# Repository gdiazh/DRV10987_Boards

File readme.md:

# DRV10987 Boards
Different custom appication eagle-boards for drv10987 BLDC motor driver

## Brief

* DRV10987: PC104-board application using a single driver and atmega328 uC
* DRV10987_SAMD21uC: PC104-board application using three drivers and samd21 uC
* mini_v1: small square board using a single driver and atmega328 uC
* mini_v2: small circle board for a single driver
* mini_v2: small circle board for a single driver
* uC_mini_v2: atmega328 uC mini-circular board
* uCsamd21_mini: samd21 uC mini-circular board

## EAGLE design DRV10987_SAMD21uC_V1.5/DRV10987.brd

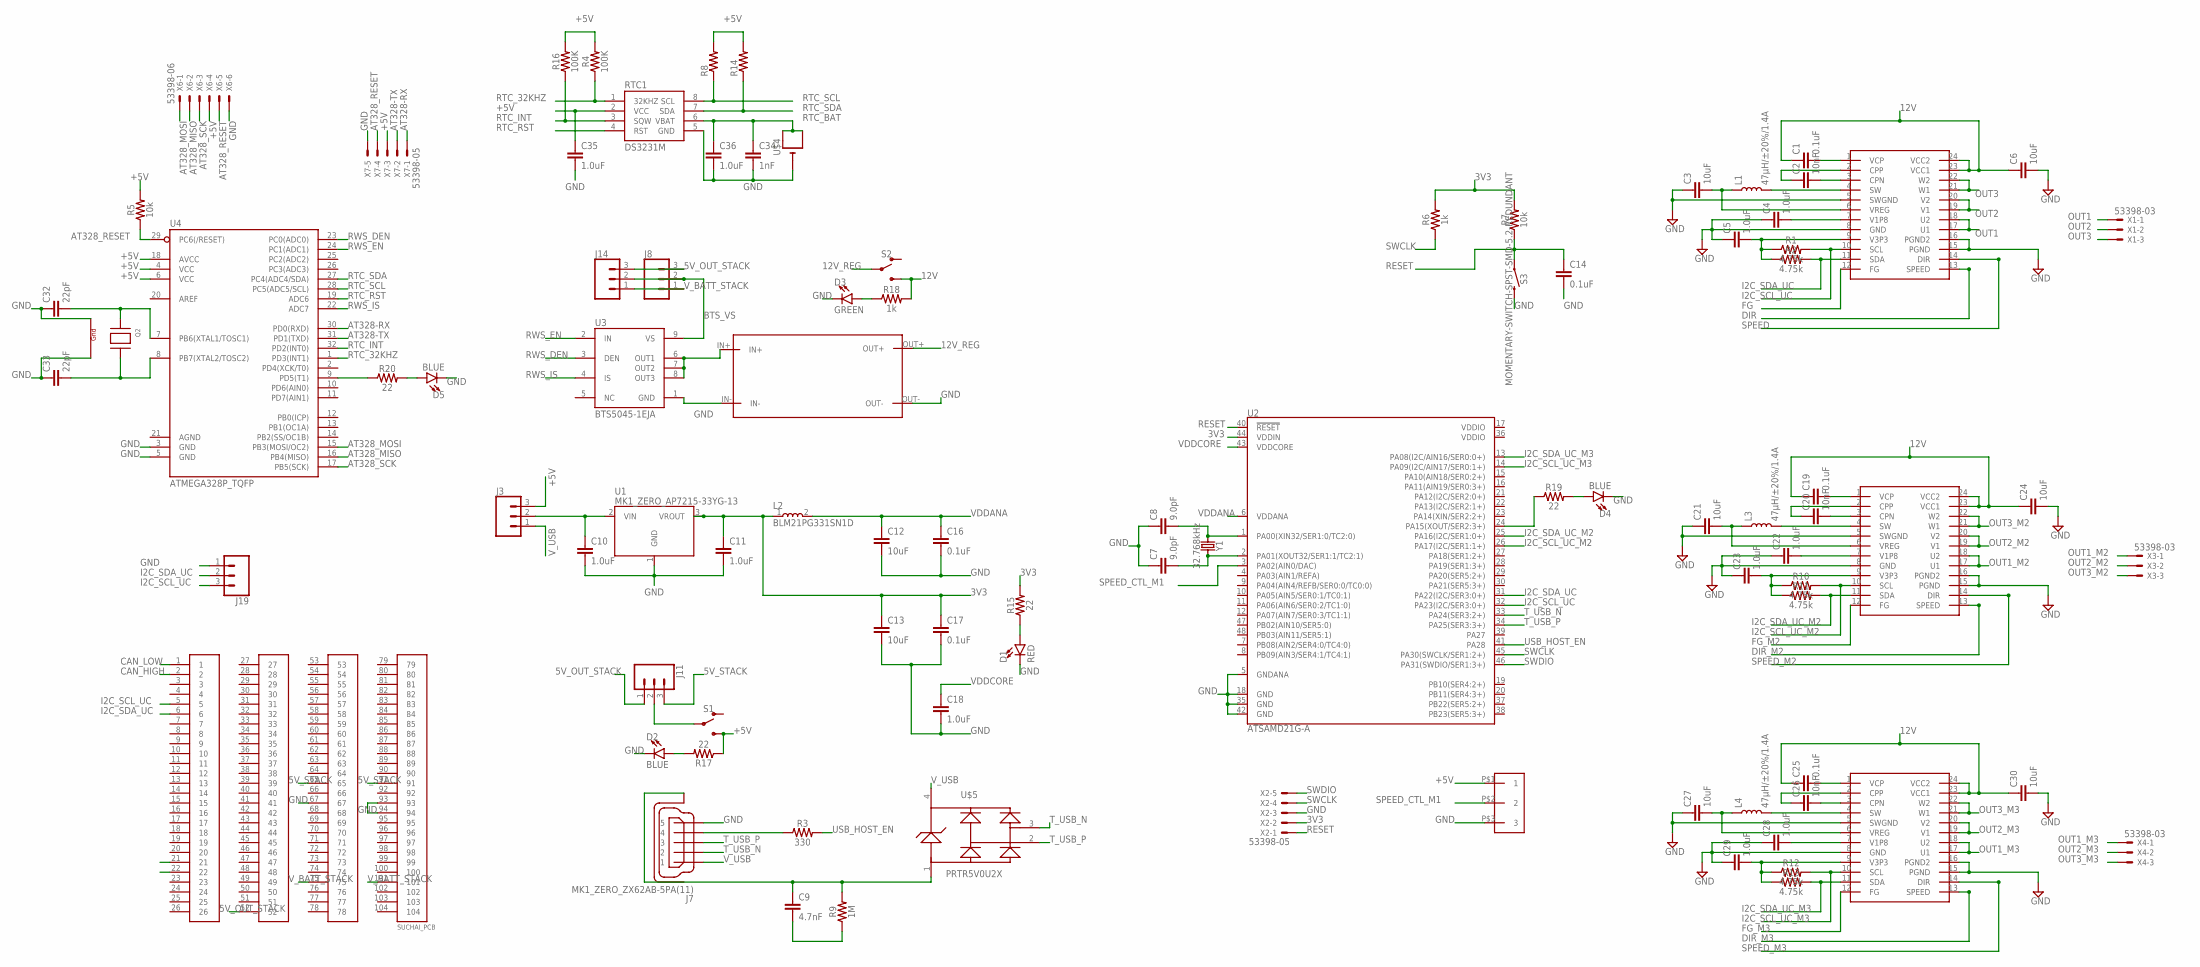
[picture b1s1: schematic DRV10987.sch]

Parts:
C1, C14, C16, C17, C19, C25: 0.1uF; 0805
C2, C20, C26: 10nF; 0805
C3, C6, C12, C13, C21, C24, C27, C30: 10uF; 0805
C4, C5, C10, C11, C18, C22, C23, C28, C29: 1.0uF; 0805
C7, C8: 9.0pF; 0603
C9: 4.7nF; 0603
C32, C33: 22pF; 0603
C34: 1nF; 0603
C35, C36: 1.0uF; 0402
D1: RED; LED-0603
D2, D4, D5: BLUE; LED-0603
D3: GREEN; LED-0603
J1: SUCHAI_PCB
J3: CONN_03LOCK_LONGPADS; 1X03_LOCK_LONGPADS
J7: MK1_ZERO_ZX62AB-5PA(11); MK1_ZERO_USBMICRO-ZX62-AB-5PA
J8, J11, J14, J19: CONN_03LOCK; 1X03_LOCK
L1, L3, L4: 47µH/±20%/1.4A; SRN6045
L2: BLM21PG331SN1D; INDC2012X87
Q2: XTAL-4-3225; NX3225
R1, R2, R10, R11, R12, R13: 4.75k; 0805
R3: 330; 0603
R4, R16: 100K; 0402
R5, R7: 10k; 0603
R6, R18: 1k; 0603
R8, R14: R-US_R0402; R0402
R9: 1M; 0603
R15, R17, R19, R20: 22; 0603
RTC1: DS3231M; SO08
S1, S2: SWITCH-SPDT-PTH-11.6X4.0MM; SWITCH_SPDT_PTH_11.6X4.0MM
S3: MOMENTARY-SWITCH-SPST-SMD-5.2-REDUNDANT; TACTILE_SWITCH_SMD_5.2MM
U1: MK1_ZERO_AP7215-33YG-13; MK1_ZERO_SOT150P400X160-3N
U2: ATSAMD21G-A; TQFP-48
U3: BTS5045-1EJA; SOIC127P600X170-9N
U4: ATMEGA328P_TQFP; TQFP32-08
U$1, U$6, U$7: DRV10987
U$2: XL6009E1_MODULE
U$3: CONN_03_SMD_SMALL
U$4: CR1220SMT; CR1220-SMD
U$5: ARDUINO_PRTR5V0U2XB; ARDUINO_SOT143B
X1, X3, X4: 53398-03
X2, X7: 53398-05
X6: 53398-06
Y1: 32.768kHz; CRYSTAL-SMD-3.2X1.5MM

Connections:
3V3: C11.1, C13.1, C17.1, L2.1, R6.2, R7.2, R15.2, U1.3 (VROUT), U2.44 (VDDIN), X2.2
5V_OUT_STACK: J1.52, J8.3, J11.1, J14.3
5V_STACK: J1.65, J1.91, J11.3
12V: C1.1, C6.1, C19.1, C24.1, C25.1, C30.1, R18.2, S2.3 (S), U$1.23 (VCC1), U$1.24 (VCC2), U$6.23 (VCC1), U$6.24 (VCC2), U$7.23 (VCC1), U$7.24 (VCC2)
12V_REG: S2.2, U$2.OUT+
+5V: C35.1, J3.3, R4.2, R5.2, R8.2, R14.2, R16.2, R17.1, RTC1.2 (VCC), S1.3 (S), U4.4 (VCC), U4.6 (VCC), U4.18 (AVCC), U$3.P$1 (1), X6.4, X7.3
AT328-RX: U4.30 (PD0(RXD)), X7.1
AT328-TX: U4.31 (PD1(TXD)), X7.2
AT328_MISO: U4.16 (PB4(MISO)), X6.2
AT328_MOSI: U4.15 (PB3(MOSI/OC2)), X6.1
AT328_RESET: R5.1, U4.29 (PC6(/RESET)), X6.5, X7.4
AT328_SCK: U4.17 (PB5(SCK)), X6.3
BTS_VS: J8.2, J14.2, U3.9 (VS)
CAN_HIGH: J1.2
CAN_LOW: J1.1
DIR: U$1.13 (SPEED)
DIR_M2: U$6.13 (SPEED)
DIR_M3: U$7.13 (SPEED)
FG: U$1.12 (FG)
FG_M2: U$6.12 (FG)
FG_M3: U$7.12 (FG)
GND: C3.1, C4.1, C5.1, C6.2, C7.1, C8.1, C10.2, C11.2, C12.2, C13.2, C14.2, C16.2, C17.2, C18.2, C21.1, C22.1, C23.1, C24.2, C27.1, C28.1, C29.1, C30.2, C32.1, C33.1, C34.2, C35.2, C36.2, D1.C, D2.C, D3.C, D4.C, D5.C, J1.67, J1.93, J1.94, J7.5, J19.1, Q2.2 (G2), Q2.4 (G1), RTC1.5 (GND), S3.3 (2), S3.4 (2), U1.1 (GND), U2.5 (GNDANA), U2.18 (GND), U2.35 (GND), U2.42 (GND), U3.1 (GND), U4.3 (GND), U4.5 (GND), U$1.5 (SWGND), U$1.8 (GND), U$1.15 (PGND), U$1.16 (PGND2), U$2.IN-, U$2.OUT-, U$3.P$3 (3), U$4.-, U$6.5 (SWGND), U$6.8 (GND), U$6.15 (PGND), U$6.16 (PGND2), U$7.5 (SWGND), U$7.8 (GND), U$7.15 (PGND), U$7.16 (PGND2), X2.3, X6.6, X7.5
I2C_SCL_UC: J1.5, J19.3, R1.2, U2.32 (PA23(I2C/SER3:0+)), U$1.10 (SCL)
I2C_SCL_UC_M2: R10.2, U2.26 (PA17(I2C/SER1:1+)), U$6.10 (SCL)
I2C_SCL_UC_M3: R12.2, U2.14 (PA09(I2C/AIN17/SER0:1+)), U$7.10 (SCL)
I2C_SDA_UC: J1.6, J19.2, R2.2, U2.31 (PA22(I2C/SER3:0+)), U$1.11 (SDA)
I2C_SDA_UC_M2: R11.2, U2.25 (PA16(I2C/SER1:0+)), U$6.11 (SDA)
I2C_SDA_UC_M3: R13.2, U2.13 (PA08(I2C/AIN16/SER0:0+)), U$7.11 (SDA)
unnamed: C1.2, U$1.1 (VCP)
unnamed: C2.1, U$1.2 (CPP)
unnamed: C2.2, U$1.3 (CPN)
unnamed: L1.2, U$1.4 (SW)
unnamed: J11.2, S1.2
unnamed: C3.2, L1.1, U$1.6 (VREG)
unnamed: C4.2, U$1.7 (V1P8)
unnamed: C7.2, U2.2 (PA01(XOUT32/SER1:1/TC2:1)), Y1.P$2 (2)
unnamed: C5.2, R1.1, R2.1, U$1.9 (V3P3)
unnamed: C8.2, U2.1 (PA00(XIN32/SER1:0/TC2:0)), Y1.P$1 (1)
unnamed: J7.4, R3.1
unnamed: U3.6 (OUT1), U3.7 (OUT2), U3.8 (OUT3), U$2.IN+
unnamed: C32.2, Q2.1 (X1), U4.7 (PB6(XTAL1/TOSC1))
unnamed: C33.2, Q2.3 (X2), U4.8 (PB7(XTAL2/TOSC2))
unnamed: D1.A, R15.1
unnamed: C9.1, J7.6 (SH), J7.7 (SH), J7.8 (SH), J7.9 (SH), J7.10 (SH), J7.11 (SH), R9.2, U$5.1
unnamed: C9.2, R9.1
unnamed: C10.1, J3.2, U1.2 (VIN)
unnamed: D2.A, R17.2
unnamed: C19.2, U$6.1 (VCP)
unnamed: C20.1, U$6.2 (CPP)
unnamed: C20.2, U$6.3 (CPN)
unnamed: L3.2, U$6.4 (SW)
unnamed: C21.2, L3.1, U$6.6 (VREG)
unnamed: C22.2, U$6.7 (V1P8)
unnamed: C23.2, R10.1, R11.1, U$6.9 (V3P3)
unnamed: C25.2, U$7.1 (VCP)
unnamed: C26.1, U$7.2 (CPP)
unnamed: C26.2, U$7.3 (CPN)
unnamed: L4.2, U$7.4 (SW)
unnamed: C27.2, L4.1, U$7.6 (VREG)
unnamed: C28.2, U$7.7 (V1P8)
unnamed: C29.2, R12.1, R13.1, U$7.9 (V3P3)
unnamed: D3.A, R18.1
unnamed: D4.A, R19.2
unnamed: R19.1, U2.24 (PA15(XOUT/SER2:3+))
unnamed: D5.A, R20.2
unnamed: R20.1, U4.9 (PD5(T1))
OUT1: U$1.17 (U1), U$1.18 (U2), X1.1
OUT1_M2: U$6.17 (U1), U$6.18 (U2), X3.1
OUT1_M3: U$7.17 (U1), U$7.18 (U2), X4.1
OUT2: U$1.19 (V1), U$1.20 (V2), X1.2
OUT2_M2: U$6.19 (V1), U$6.20 (V2), X3.2
OUT2_M3: U$7.19 (V1), U$7.20 (V2), X4.2
OUT3: U$1.21 (W1), U$1.22 (W2), X1.3
OUT3_M2: U$6.21 (W1), U$6.22 (W2), X3.3
OUT3_M3: U$7.21 (W1), U$7.22 (W2), X4.3
RESET: C14.1, R7.1, S3.1, S3.2 (1), U2.40 (!RESET!), X2.1
RTC_32KHZ: R4.1, RTC1.1 (32KHZ), U4.1 (PD3(INT1))
RTC_BAT: C34.1, C36.1, RTC1.6 (VBAT), U$4.+$1 (+), U$4.+$2 (+1)
RTC_INT: R16.1, RTC1.3 (SQW), U4.32 (PD2(INT0))
RTC_RST: RTC1.4 (RST), U4.19 (ADC6)
RTC_SCL: R8.1, RTC1.8 (SCL), U4.28 (PC5(ADC5/SCL))
RTC_SDA: R14.1, RTC1.7 (SDA), U4.27 (PC4(ADC4/SDA))
RWS_DEN: U3.3 (DEN), U4.23 (PC0(ADC0))
RWS_EN: U3.2 (IN), U4.24 (PC1(ADC1))
RWS_IS: U3.4 (IS), U4.22 (ADC7)
SPEED: U$1.14 (DIR)
SPEED_CTL_M1: U2.3 (PA02(AIN0/DAC)), U$3.P$2 (2)
SPEED_M2: U$6.14 (DIR)
SPEED_M3: U$7.14 (DIR)
SWCLK: R6.1, U2.45 (PA30(SWCLK/SER1:2+)), X2.4
SWDIO: U2.46 (PA31(SWDIO/SER1:3+)), X2.5
T_USB_N: J7.2, U2.33 (PA24(SER3:2+)), U$5.3
T_USB_P: J7.3, U2.34 (PA25(SER3:3+)), U$5.2
USB_HOST_EN: R3.2, U2.41 (PA28)
VDDANA: C12.1, C16.1, L2.2, U2.6 (VDDANA)
VDDCORE: C18.1, U2.43 (VDDCORE)
V_BATT_STACK: J1.75, J1.101, J8.1, J14.1
V_USB: J3.1, J7.1, U$5.4

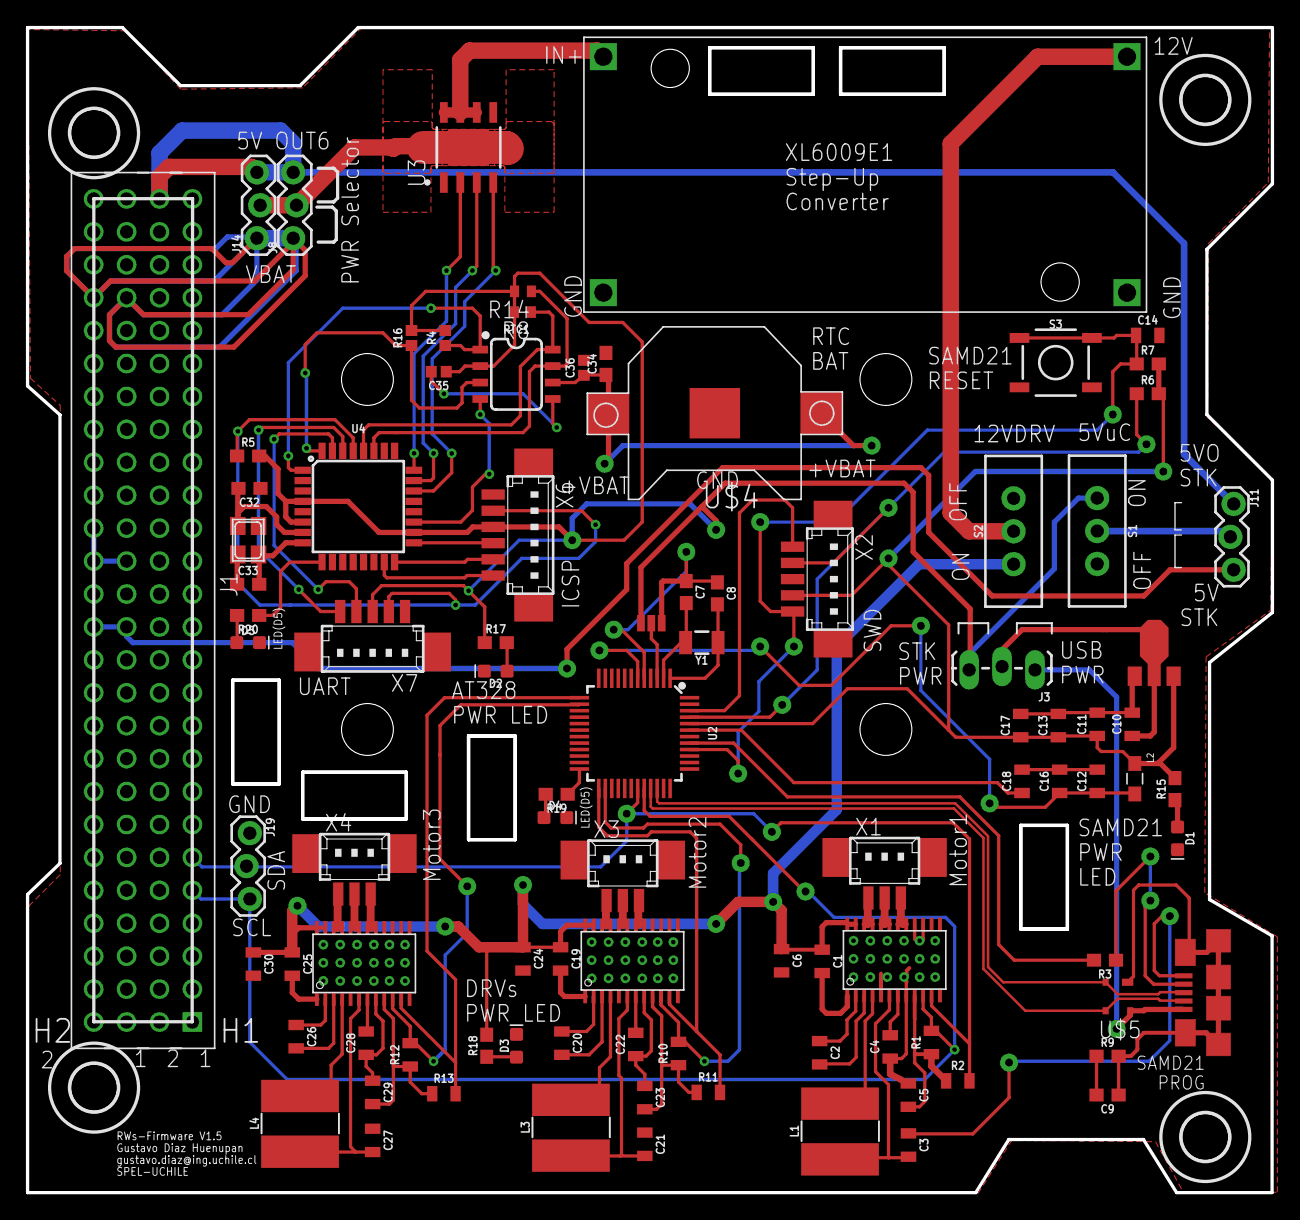
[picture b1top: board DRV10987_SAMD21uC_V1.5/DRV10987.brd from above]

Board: 2 copper layers, 96.0 x 89.9 mm, 93 parts (0 on the bottom side), 87 nets.

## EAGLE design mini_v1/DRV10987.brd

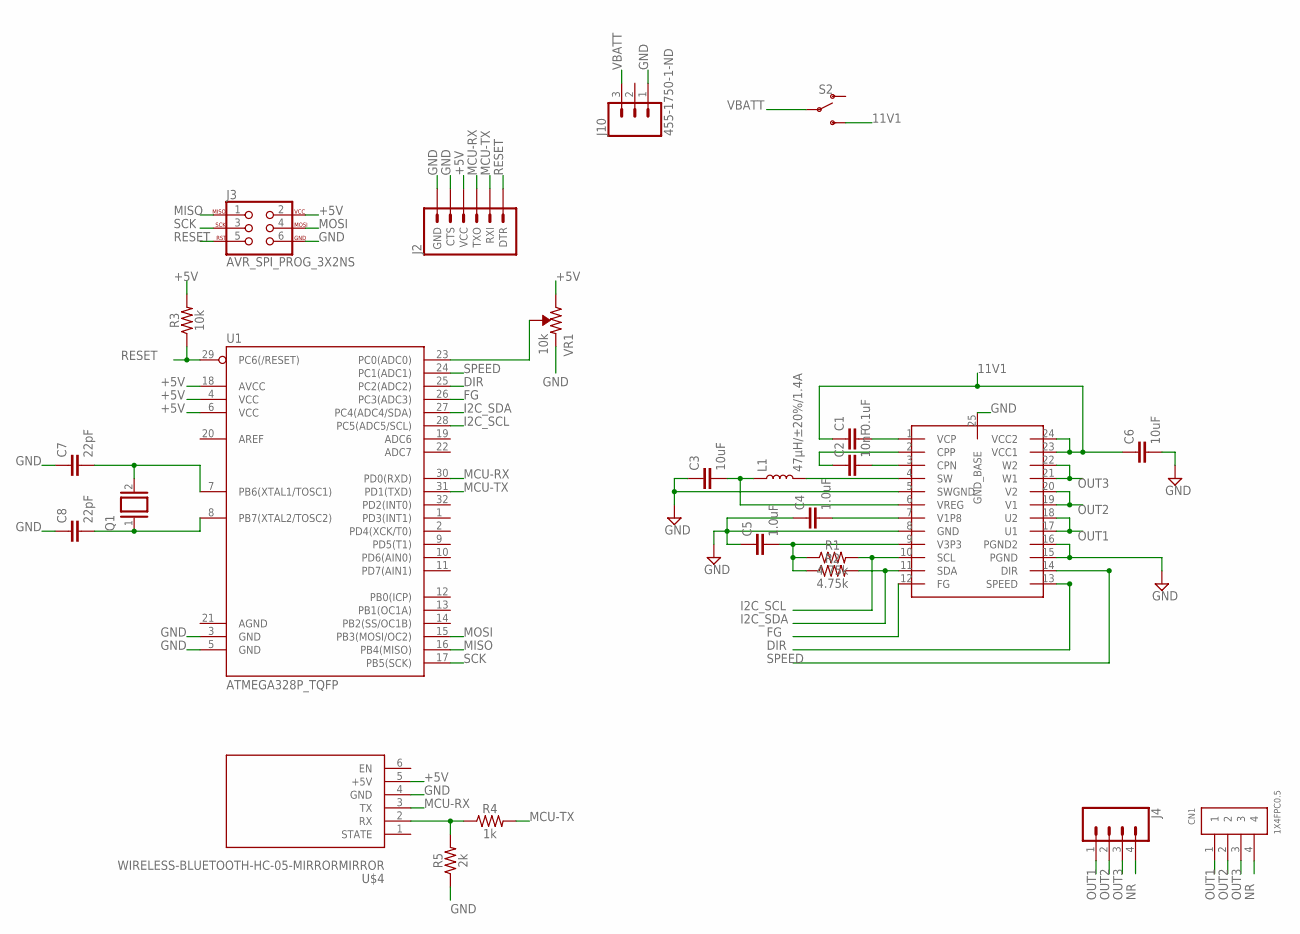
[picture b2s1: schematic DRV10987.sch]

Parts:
C1: 0.1uF; 0805
C2: 10nF; 0805
C3, C6: 10uF; 0805
C4, C5: 1.0uF; 0805
C7, C8: 22pF; 1206
CN1: 1X4FPC0.5; FPC_0.5MM-4
J2: 6_PIN_SERIAL_TARGET; 1X06
J3: AVR_SPI_PROG_3X2NS; 2X3-NS
J4: CONN_04; 1X04
J10: 455-1750-1-ND; 1X03
L1: 47µH/±20%/1.4A; SRN6045
Q1: XTAL/S; QS
R1, R2: 4.75k; 0805
R3: 10k; 1206
R4: 1k; AXIAL-0.3
R5: 2k; AXIAL-0.3
S2: SWITCH-SPDT-PTH-11.6X4.0MM; SWITCH_SPDT_PTH_11.6X4.0MM
U1: ATMEGA328P_TQFP; TQFP32-08
U$1: DRV10987
U$4: WIRELESS-BLUETOOTH-HC-05-MIRRORMIRROR; WIRELESS-BLUETOOTH-HC-05-MIRROR
VR1: 10k; TRIMPOT-PTH-3386U

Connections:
11V1: C1.1, C6.1, S2.3 (S), U$1.23 (VCC1), U$1.24 (VCC2)
+5V: J2.4 (VCC), J3.2, R3.2, U1.4 (VCC), U1.6 (VCC), U1.18 (AVCC), U$4.5 (+5V), VR1.3 (CW)
DIR: U1.25 (PC2(ADC2)), U$1.13 (SPEED)
FG: U1.26 (PC3(ADC3)), U$1.12 (FG)
GND: C3.1, C4.1, C5.1, C6.2, C7.1, C8.1, J2.5 (CTS), J2.6 (GND), J3.6, J10.1, R5.P$1 (1), U1.3 (GND), U1.5 (GND), U$1.5 (SWGND), U$1.8 (GND), U$1.15 (PGND), U$1.16 (PGND2), U$1.25 (GND_BASE), U$4.4 (GND), VR1.1 (CCW)
I2C_SCL: R1.2, U1.28 (PC5(ADC5/SCL)), U$1.10 (SCL)
I2C_SDA: R2.2, U1.27 (PC4(ADC4/SDA)), U$1.11 (SDA)
MCU-RX: J2.3 (TXO), U1.30 (PD0(RXD)), U$4.3 (TX)
MCU-TX: J2.2 (RXI), R4.P$2 (2), U1.31 (PD1(TXD))
MISO: J3.1, U1.16 (PB4(MISO))
MOSI: J3.4, U1.15 (PB3(MOSI/OC2))
unnamed: C1.2, U$1.1 (VCP)
unnamed: C2.1, U$1.2 (CPP)
unnamed: C2.2, U$1.3 (CPN)
unnamed: L1.2, U$1.4 (SW)
unnamed: C3.2, L1.1, U$1.6 (VREG)
unnamed: C4.2, U$1.7 (V1P8)
unnamed: C7.2, Q1.2, U1.7 (PB6(XTAL1/TOSC1))
unnamed: C5.2, R1.1, R2.1, U$1.9 (V3P3)
unnamed: C8.2, Q1.1, U1.8 (PB7(XTAL2/TOSC2))
unnamed: R4.P$1 (1), R5.P$2 (2), U$4.2 (RX)
unnamed: U1.23 (PC0(ADC0)), VR1.2 (WIPER)
NR: CN1.4, J4.4
OUT1: CN1.1, J4.1, U$1.17 (U1), U$1.18 (U2)
OUT2: CN1.2, J4.2, U$1.19 (V1), U$1.20 (V2)
OUT3: CN1.3, J4.3, U$1.21 (W1), U$1.22 (W2)
RESET: J2.1 (DTR), J3.5, R3.1, U1.29 (PC6(/RESET))
SCK: J3.3, U1.17 (PB5(SCK))
SPEED: U1.24 (PC1(ADC1)), U$1.14 (DIR)
VBATT: J10.3, S2.2

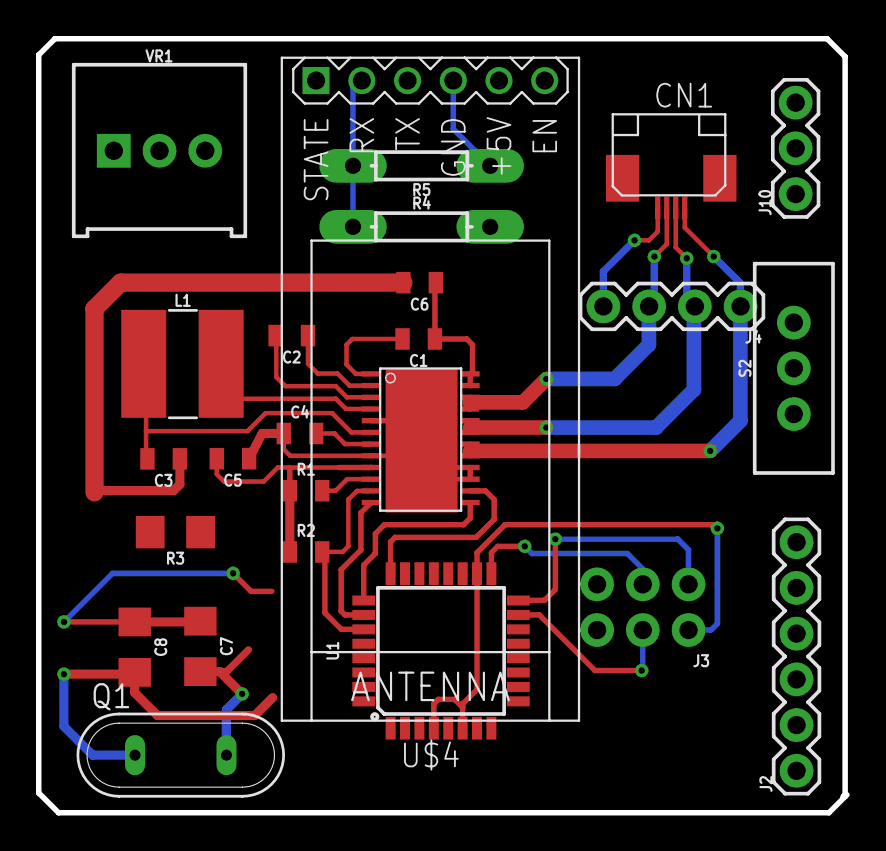
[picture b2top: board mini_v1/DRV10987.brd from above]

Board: 2 copper layers, 44.9 x 43.0 mm, 25 parts (0 on the bottom side), 30 nets.

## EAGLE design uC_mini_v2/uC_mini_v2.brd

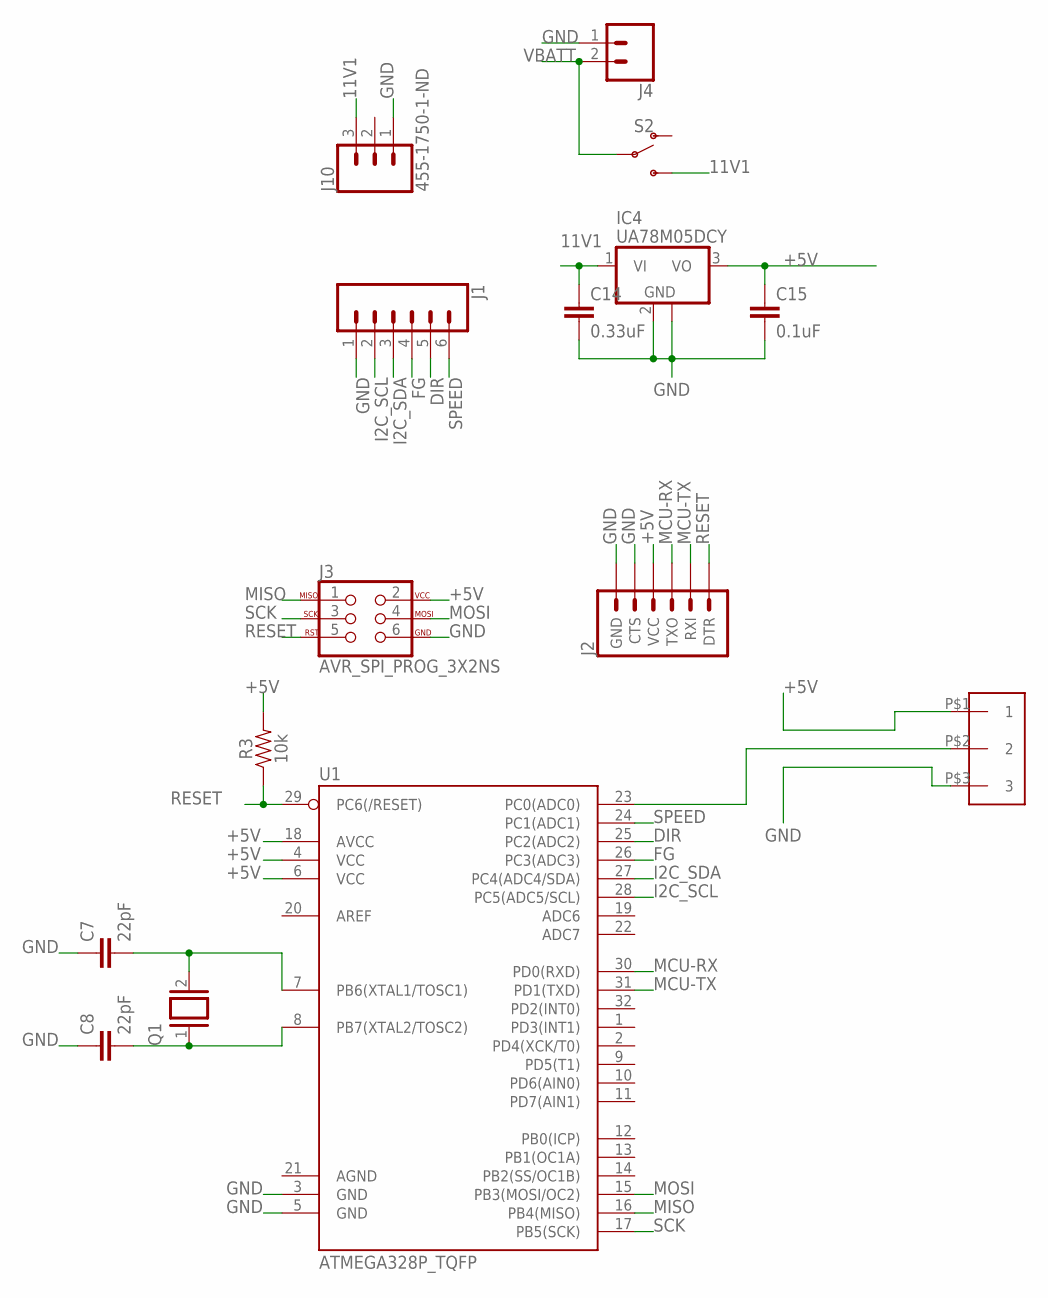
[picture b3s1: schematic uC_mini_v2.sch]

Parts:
C7, C8: 22pF; 1206
C14: 0.33uF; 1206
C15: 0.1uF; 1206
IC4: UA78M05DCY; SOT223
J1: CONN_06LOCK; 1X06_LOCK
J2: 6_PIN_SERIAL_TARGET; 1X06
J3: AVR_SPI_PROG_3X2NS; 2X3-NS
J4: CONN_02LOCK; 1X02_LOCK
J10: 455-1750-1-ND; 1X03
Q1: XTAL/S; QS
R3: 10k; 1206
S2: SWITCH-SPDT-PTH-11.6X4.0MM; SWITCH_SPDT_PTH_11.6X4.0MM
U1: ATMEGA328P_TQFP; TQFP32-08
U$3: CONN_03_SMD_SMALL

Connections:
11V1: C14.1, IC4.1 (VI), J10.3, S2.3 (S)
+5V: C15.1, IC4.3 (VO), J2.4 (VCC), J3.2, R3.2, U1.4 (VCC), U1.6 (VCC), U1.18 (AVCC), U$3.P$1 (1)
DIR: J1.5, U1.25 (PC2(ADC2))
FG: J1.4, U1.26 (PC3(ADC3))
GND: C7.1, C8.1, C14.2, C15.2, IC4.2 (GND), IC4.4 (GND), J1.1, J2.5 (CTS), J2.6 (GND), J3.6, J4.1, J10.1, U1.3 (GND), U1.5 (GND), U$3.P$3 (3)
I2C_SCL: J1.2, U1.28 (PC5(ADC5/SCL))
I2C_SDA: J1.3, U1.27 (PC4(ADC4/SDA))
MCU-RX: J2.3 (TXO), U1.30 (PD0(RXD))
MCU-TX: J2.2 (RXI), U1.31 (PD1(TXD))
MISO: J3.1, U1.16 (PB4(MISO))
MOSI: J3.4, U1.15 (PB3(MOSI/OC2))
unnamed: C7.2, Q1.2, U1.7 (PB6(XTAL1/TOSC1))
unnamed: C8.2, Q1.1, U1.8 (PB7(XTAL2/TOSC2))
unnamed: U1.23 (PC0(ADC0)), U$3.P$2 (2)
RESET: J2.1 (DTR), J3.5, R3.1, U1.29 (PC6(/RESET))
SCK: J3.3, U1.17 (PB5(SCK))
SPEED: J1.6, U1.24 (PC1(ADC1))
VBATT: J4.2, S2.2

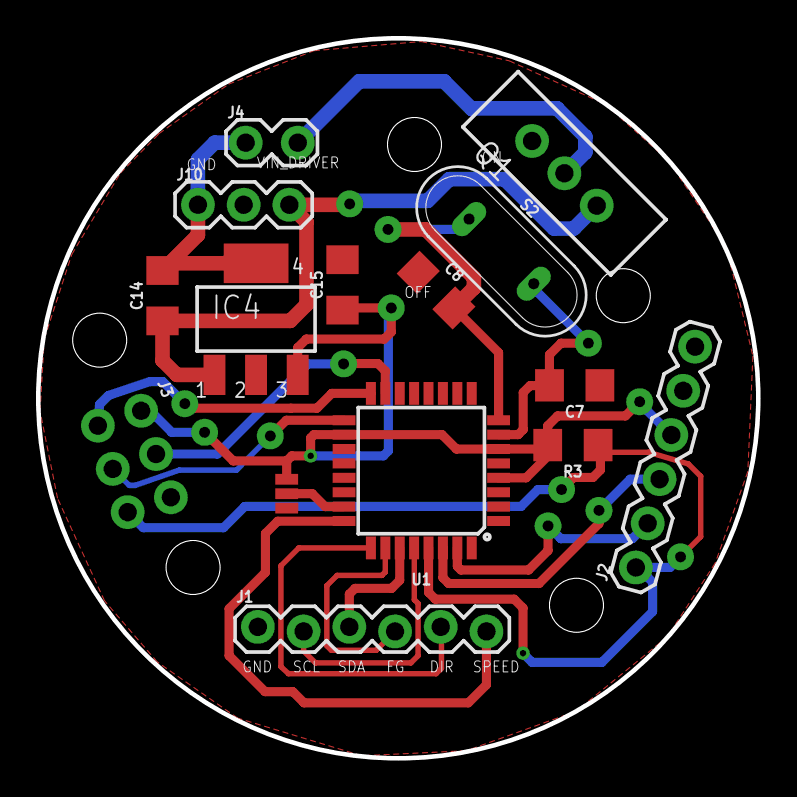
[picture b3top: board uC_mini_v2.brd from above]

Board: 2 copper layers, 40.0 x 40.0 mm, 15 parts (0 on the bottom side), 18 nets.

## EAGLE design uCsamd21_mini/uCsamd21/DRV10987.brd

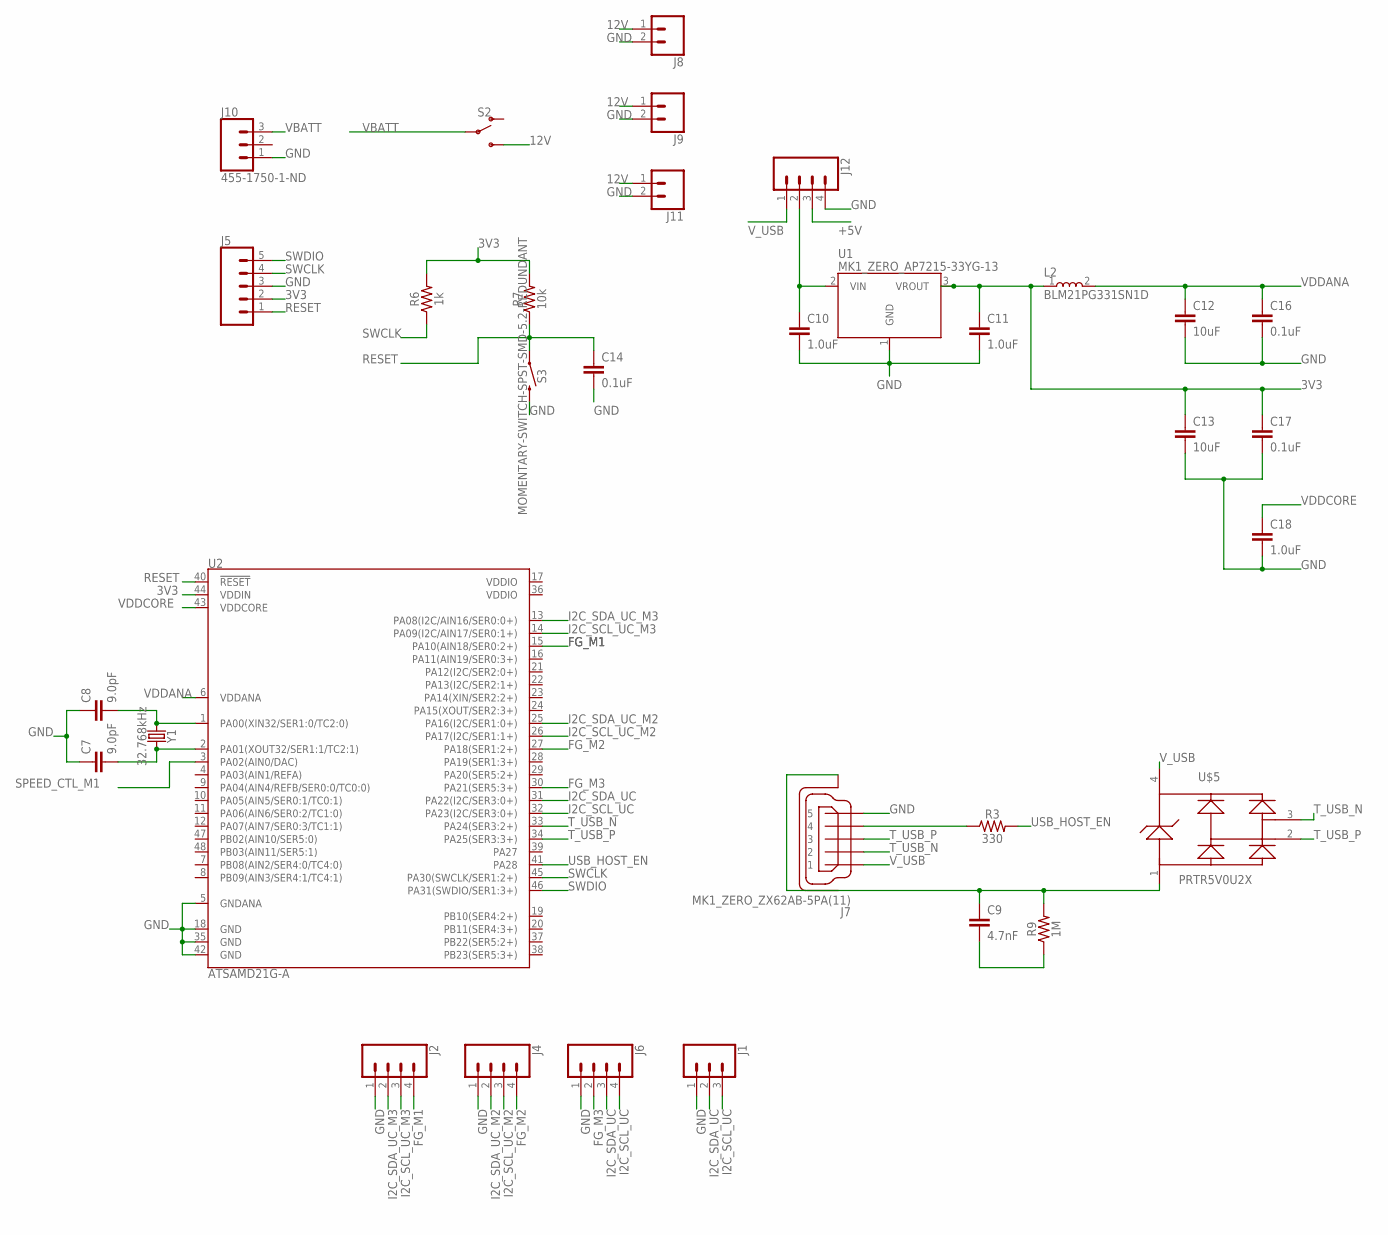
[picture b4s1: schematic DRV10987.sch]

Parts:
C7, C8: 9.0pF; 0603
C9: 4.7nF; 0603
C10, C11, C18: 1.0uF; 0805
C12, C13: 10uF; 0805
C14, C16, C17: 0.1uF; 0805
J1: CONN_03LOCK; 1X03_LOCK
J2, J4, J6, J12: CONN_04LOCK; 1X04_LOCK
J5: CONN_05LOCK_LONGPADS; 1X05_LOCK_LONGPADS
J7: MK1_ZERO_ZX62AB-5PA(11); MK1_ZERO_USBMICRO-ZX62-AB-5PA
J8, J9, J11: CONN_02LOCK; 1X02_LOCK
J10: 455-1750-1-ND; 1X03
L2: BLM21PG331SN1D; INDC2012X87
R3: 330; 0603
R6: 1k; 0603
R7: 10k; 0603
R9: 1M; 0603
S2: SWITCH-SPDT-PTH-11.6X4.0MM; SWITCH_SPDT_PTH_11.6X4.0MM
S3: MOMENTARY-SWITCH-SPST-SMD-5.2-REDUNDANT; TACTILE_SWITCH_SMD_5.2MM
U1: MK1_ZERO_AP7215-33YG-13; MK1_ZERO_SOT150P400X160-3N
U2: ATSAMD21G-A; TQFP-48
U$5: ARDUINO_PRTR5V0U2XB; ARDUINO_SOT143B
Y1: 32.768kHz; CRYSTAL-SMD-3.2X1.5MM

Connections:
3V3: C11.1, C13.1, C17.1, J5.2, L2.1, R6.2, R7.2, U1.3 (VROUT), U2.44 (VDDIN)
12V: J8.1, J9.1, J11.1, S2.3 (S)
+5V: J12.3
FG_M1: J2.4, U2.15 (PA10(AIN18/SER0:2+))
FG_M2: J4.4, U2.27 (PA18(SER1:2+))
FG_M3: J6.2, U2.30 (PA21(SER5:3+))
GND: C7.1, C8.1, C10.2, C11.2, C12.2, C13.2, C14.2, C16.2, C17.2, C18.2, J1.1, J2.1, J4.1, J5.3, J6.1, J7.5, J8.2, J9.2, J10.1, J11.2, J12.4, S3.3 (2), S3.4 (2), U1.1 (GND), U2.5 (GNDANA), U2.18 (GND), U2.35 (GND), U2.42 (GND)
I2C_SCL_UC: J1.3, J6.4, U2.32 (PA23(I2C/SER3:0+))
I2C_SCL_UC_M2: J4.3, U2.26 (PA17(I2C/SER1:1+))
I2C_SCL_UC_M3: J2.3, U2.14 (PA09(I2C/AIN17/SER0:1+))
I2C_SDA_UC: J1.2, J6.3, U2.31 (PA22(I2C/SER3:0+))
I2C_SDA_UC_M2: J4.2, U2.25 (PA16(I2C/SER1:0+))
I2C_SDA_UC_M3: J2.2, U2.13 (PA08(I2C/AIN16/SER0:0+))
unnamed: J7.4, R3.1
unnamed: C7.2, U2.2 (PA01(XOUT32/SER1:1/TC2:1)), Y1.P$2 (2)
unnamed: C8.2, U2.1 (PA00(XIN32/SER1:0/TC2:0)), Y1.P$1 (1)
unnamed: C9.1, J7.6 (SH), J7.7 (SH), J7.8 (SH), J7.9 (SH), J7.10 (SH), J7.11 (SH), R9.2, U$5.1
unnamed: C9.2, R9.1
unnamed: C10.1, J12.2, U1.2 (VIN)
RESET: C14.1, J5.1, R7.1, S3.1, S3.2 (1), U2.40 (!RESET!)
SPEED_CTL_M1: U2.3 (PA02(AIN0/DAC))
SWCLK: J5.4, R6.1, U2.45 (PA30(SWCLK/SER1:2+))
SWDIO: J5.5, U2.46 (PA31(SWDIO/SER1:3+))
T_USB_N: J7.2, U2.33 (PA24(SER3:2+)), U$5.3
T_USB_P: J7.3, U2.34 (PA25(SER3:3+)), U$5.2
USB_HOST_EN: R3.2, U2.41 (PA28)
VBATT: J10.3, S2.2
VDDANA: C12.1, C16.1, L2.2, U2.6 (VDDANA)
VDDCORE: C18.1, U2.43 (VDDCORE)
V_USB: J7.1, J12.1, U$5.4

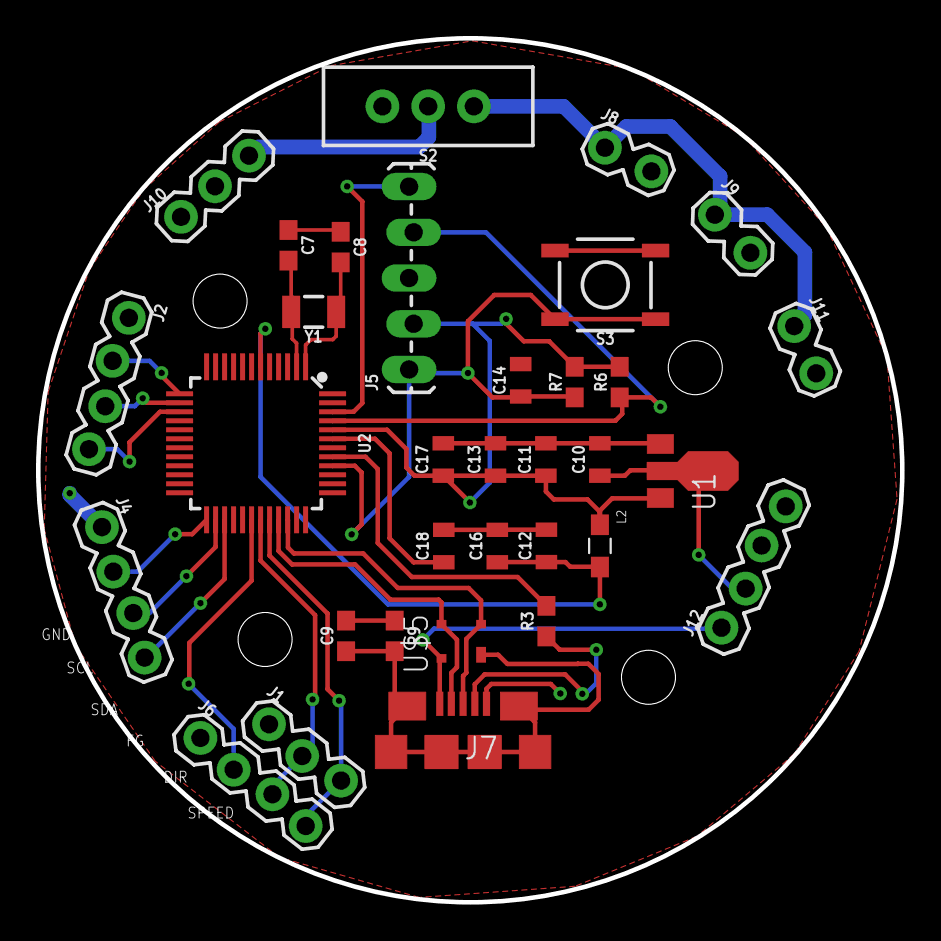
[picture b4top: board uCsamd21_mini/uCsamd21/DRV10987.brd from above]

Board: 2 copper layers, 48.0 x 48.0 mm, 33 parts (0 on the bottom side), 28 nets.

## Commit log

2020-07-27 versioning
2020-08-12 new SAMD21uC_v1.5, added BTS5045, molex connectors, remove conf jumpers, and added holes for wires
2020-08-15 added rtc, atmega328, leds, labels and adjust usb connector

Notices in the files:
parts and their libraries:
SparkFun-Capacitors: Licensing: Creative Commons ShareAlike 4.0 International - https://creativecommons.org/licenses/by-sa/4.0
diy-modules: Released under the Creative Commons Attribution 4.0 International License: http://creativecommons.org/licenses/by/4.0
